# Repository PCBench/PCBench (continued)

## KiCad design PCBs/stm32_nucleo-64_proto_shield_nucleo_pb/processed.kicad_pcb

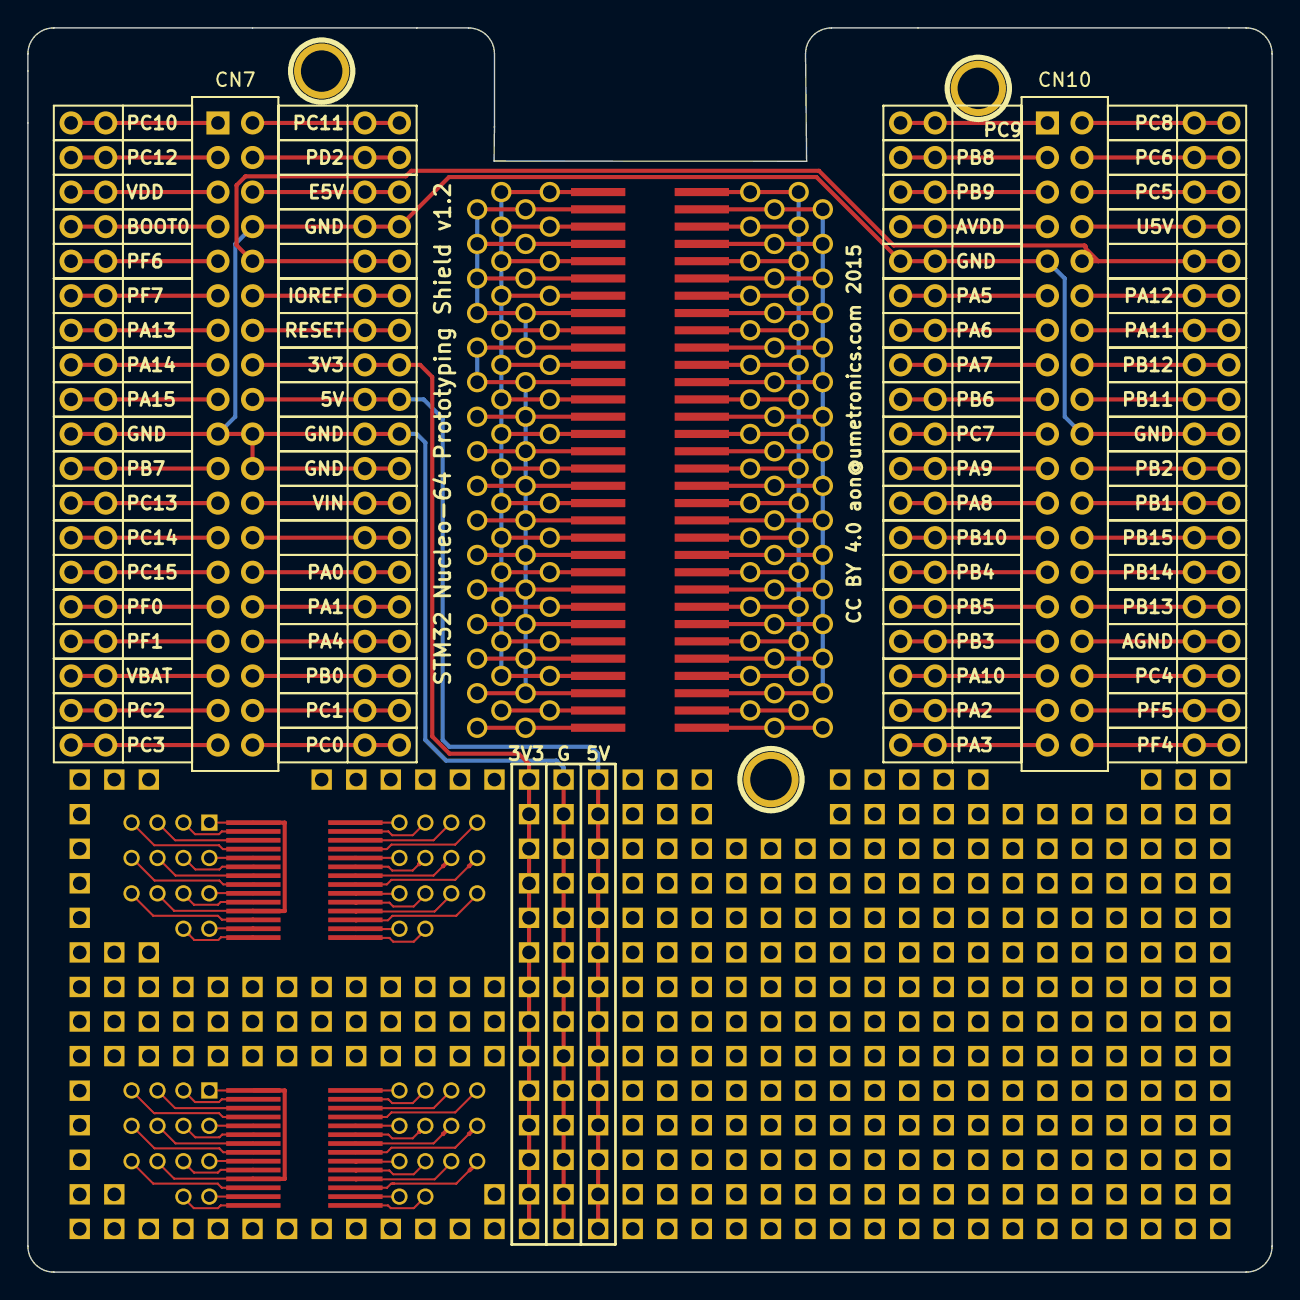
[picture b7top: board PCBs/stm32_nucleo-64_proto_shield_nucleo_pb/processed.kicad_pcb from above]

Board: 2 copper layers, 91.4 x 91.4 mm, 273 parts (0 on the bottom side), 132 nets.

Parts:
1PIN, 1PIN_2, 1PIN_3: P***; 1pin
CN7, CN10: 2X19_HEADER; PIN_ARRAY_19X2
P1, P2, P3, P4, P5, P6, P7, P8, P9, P10, P11, P12, P13, P14, P15, P16, P17, P18, P19, P20, P21, P22, P23, P24, P25, P26, P27, P28, P29, P30, P31, P32, P33, P34, P35, P36, P37, P38, P39, P40, P41, P42, P43, P44, P45, P46, P47, P48, P49, P50, P51, P52, P53, P54, P55, P56, P57, P58, P59, P60, P61, P62, P63, P64, P65, P66, P67, P68, P69, P70, P71, P72, P73, P74, P75, P76: CONN_2
P77, P77_2, P77_3, P77_4, P77_5, P77_6, P77_7, P77_8, P77_9, P77_10, P77_11, P77_12, P77_13, P77_14, P77_15, P77_16: SOIC_AREA
PROTO_1PIN, PROTO_1PIN_2, PROTO_1PIN_3, PROTO_1PIN_4, PROTO_1PIN_5, PROTO_1PIN_6, PROTO_1PIN_7, PROTO_1PIN_8, PROTO_1PIN_9, PROTO_1PIN_10, PROTO_1PIN_11, PROTO_1PIN_12, PROTO_1PIN_13, PROTO_1PIN_14, PROTO_1PIN_15, PROTO_1PIN_16, PROTO_1PIN_17, PROTO_1PIN_18, PROTO_1PIN_19, PROTO_1PIN_20, PROTO_1PIN_21, PROTO_1PIN_22, PROTO_1PIN_23, PROTO_1PIN_24, PROTO_1PIN_25, PROTO_1PIN_26, PROTO_1PIN_27, PROTO_1PIN_28, PROTO_1PIN_29, PROTO_1PIN_30, PROTO_1PIN_31, PROTO_1PIN_32, PROTO_1PIN_33, PROTO_1PIN_34, PROTO_1PIN_35, PROTO_1PIN_36, PROTO_1PIN_37, PROTO_1PIN_38, PROTO_1PIN_39, PROTO_1PIN_40, PROTO_1PIN_41, PROTO_1PIN_42, PROTO_1PIN_43, PROTO_1PIN_44, PROTO_1PIN_45, PROTO_1PIN_46, PROTO_1PIN_47, PROTO_1PIN_48, PROTO_1PIN_49, PROTO_1PIN_50, PROTO_1PIN_51, PROTO_1PIN_52, PROTO_1PIN_53, PROTO_1PIN_54, PROTO_1PIN_55, PROTO_1PIN_56, PROTO_1PIN_57, PROTO_1PIN_58, PROTO_1PIN_59, PROTO_1PIN_60, PROTO_1PIN_61, PROTO_1PIN_62, PROTO_1PIN_63, PROTO_1PIN_64, PROTO_1PIN_65, PROTO_1PIN_66, PROTO_1PIN_67, PROTO_1PIN_68, PROTO_1PIN_69, PROTO_1PIN_70, PROTO_1PIN_71, PROTO_1PIN_72, PROTO_1PIN_73, PROTO_1PIN_74, PROTO_1PIN_75, PROTO_1PIN_76, PROTO_1PIN_77, PROTO_1PIN_78, PROTO_1PIN_79, PROTO_1PIN_80, PROTO_1PIN_81, PROTO_1PIN_82, PROTO_1PIN_83, PROTO_1PIN_84, PROTO_1PIN_85, PROTO_1PIN_86, PROTO_1PIN_87, PROTO_1PIN_88, PROTO_1PIN_89, PROTO_1PIN_90, PROTO_1PIN_91, PROTO_1PIN_92, PROTO_1PIN_93, PROTO_1PIN_94, PROTO_1PIN_95, PROTO_1PIN_96, PROTO_1PIN_97, PROTO_1PIN_98, PROTO_1PIN_99, PROTO_1PIN_100, PROTO_1PIN_101, PROTO_1PIN_102, PROTO_1PIN_103, PROTO_1PIN_104, PROTO_1PIN_105, PROTO_1PIN_106, PROTO_1PIN_107, PROTO_1PIN_108, PROTO_1PIN_109, PROTO_1PIN_110, PROTO_1PIN_111, PROTO_1PIN_112, PROTO_1PIN_113, PROTO_1PIN_114, PROTO_1PIN_115, PROTO_1PIN_116, PROTO_1PIN_117, PROTO_1PIN_118, PROTO_1PIN_119, PROTO_1PIN_120, PROTO_1PIN_121, PROTO_1PIN_122, PROTO_1PIN_123, PROTO_1PIN_124, PROTO_1PIN_125, PROTO_1PIN_126, PROTO_1PIN_127, PROTO_1PIN_128, PROTO_1PIN_129, PROTO_1PIN_130, PROTO_1PIN_131, PROTO_1PIN_132, PROTO_1PIN_133, PROTO_1PIN_134, PROTO_1PIN_135, PROTO_1PIN_136, PROTO_1PIN_137, PROTO_1PIN_138, PROTO_1PIN_139, PROTO_1PIN_140, PROTO_1PIN_141, PROTO_1PIN_142, PROTO_1PIN_143, PROTO_1PIN_144, PROTO_1PIN_145, PROTO_1PIN_146, PROTO_1PIN_147, PROTO_1PIN_148, PROTO_1PIN_149, PROTO_1PIN_150, PROTO_1PIN_151: VAL**; PROTO_1PIN
PROTO_AREA: VAL**; PROTO_AREA
PROTO_AREA_2, PROTO_AREA_3, PROTO_AREA_4, PROTO_AREA_5, PROTO_AREA_6, PROTO_AREA_7, PROTO_AREA_8, PROTO_AREA_9, PROTO_AREA_10, PROTO_AREA_11, PROTO_AREA_12, PROTO_AREA_13, PROTO_AREA_14, PROTO_AREA_15, PROTO_AREA_16, PROTO_AREA_17, PROTO_AREA_18, PROTO_AREA_19, PROTO_AREA_20, PROTO_AREA_21, PROTO_AREA_22, PROTO_AREA_23: VAL**; PROTO_AREA
U1, U1_2: TSSOP28_BREAKOUT

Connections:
/3V3: CN7.16, P27.1, P27.2, PROTO_1PIN_65.10, PROTO_1PIN_75.10, PROTO_1PIN_76.10, PROTO_1PIN_77.10, PROTO_1PIN_78.10, PROTO_1PIN_79.10, PROTO_1PIN_84.10, PROTO_1PIN_88.10, PROTO_1PIN_89.10, PROTO_1PIN_90.10, PROTO_1PIN_91.10, PROTO_AREA_8.3, PROTO_AREA_8.4, PROTO_AREA_8.5
/5V: CN7.18, P28.1, P28.2, PROTO_1PIN_25.10, PROTO_1PIN_63.10, PROTO_AREA_20.1, PROTO_AREA_20.7, PROTO_AREA_20.8, PROTO_AREA_21.2, PROTO_AREA_21.6, PROTO_AREA_21.9, PROTO_AREA_22.2, PROTO_AREA_22.6, PROTO_AREA_22.9, PROTO_AREA_23.1, PROTO_AREA_23.7, PROTO_AREA_23.8
/AGND: CN10.32, P73.1, P73.2
/AVDD: CN10.7, P42.1, P42.2
/BOOT0: CN7.7, P4.1, P4.2
/E5V: CN7.6, P22.1, P22.2
/GND: CN7.8, CN7.19, CN7.20, CN7.22, CN10.9, CN10.20, P10.1, P10.2, P23.1, P23.2, P29.1, P29.2, P30.1, P30.2, P43.1, P43.2, P67.1, P67.2, PROTO_1PIN_64.10, PROTO_1PIN_80.10, PROTO_1PIN_81.10, PROTO_1PIN_82.10, PROTO_1PIN_83.10, PROTO_1PIN_85.10, PROTO_1PIN_86.10, PROTO_1PIN_87.10, PROTO_AREA_21.1, PROTO_AREA_21.7, PROTO_AREA_21.8, PROTO_AREA_22.1, PROTO_AREA_22.7, PROTO_AREA_22.8
/IOREF: CN7.12, P25.1, P25.2
/NC10: CN7.10, CN10.10, P24.1, P24.2, P62.1, P62.2
/NC26: CN7.26, P32.1, P32.2
/PA0: CN7.28, P33.1, P33.2
/PA1: CN7.30, P34.1, P34.2
/PA2: CN10.35, P56.1, P56.2
/PA3: CN10.37, P57.1, P57.2
/PA4: CN7.32, P35.1, P35.2
/PA5: CN10.11, P44.1, P44.2
/PA6: CN10.13, P45.1, P45.2
/PA7: CN10.15, P46.1, P46.2
/PA8: CN10.23, P50.1, P50.2
/PA9: CN10.21, P49.1, P49.2
/PA10: CN10.33, P55.1, P55.2
/PA11: CN10.14, P64.1, P64.2
/PA12: CN10.12, P63.1, P63.2
/PA13: CN7.13, P7.1, P7.2
/PA14: CN7.15, P8.1, P8.2
/PA15: CN7.17, P9.1, P9.2
/PB0: CN7.34, P36.1, P36.2
/PB1: CN10.24, P69.1, P69.2
/PB2: CN10.22, P68.1, P68.2
/PB3: CN10.31, P54.1, P54.2
/PB4: CN10.27, P52.1, P52.2
/PB5: CN10.29, P53.1, P53.2
/PB6: CN10.17, P47.1, P47.2
/PB7: CN7.21, P11.1, P11.2
/PB8: CN10.3, P40.1, P40.2
/PB9: CN10.5, P41.1, P41.2
/PB10: CN10.25, P51.1, P51.2
/PB11: CN10.18, P66.1, P66.2
/PB12: CN10.16, P65.1, P65.2
/PB13: CN10.30, P72.1, P72.2
/PB14: CN10.28, P71.1, P71.2
/PB15: CN10.26, P70.1, P70.2
/PC0: CN7.38, P38.1, P38.2
/PC1: CN7.36, P37.1, P37.2
/PC2: CN7.35, P18.1, P18.2
/PC3: CN7.37, P19.1, P19.2
/PC4: CN10.34, P74.1, P74.2
/PC5: CN10.6, P60.1, P60.2
/PC6: CN10.4, P59.1, P59.2
/PC7: CN10.19, P48.1, P48.2
/PC8: CN10.2, P58.1, P58.2
/PC9: CN10.1, P39.1, P39.2
/PC10: CN7.1, P1.1, P1.2
/PC11: CN7.2, P20.1, P20.2
/PC12: CN7.3, P2.1, P2.2
/PC13: CN7.23, P12.1, P12.2
/PC14: CN7.25, P13.1, P13.2
/PC15: CN7.27, P14.1, P14.2
/PD2: CN7.4, P21.1, P21.2
/PF0: CN7.29, P15.1, P15.2
/PF1: CN7.31, P16.1, P16.2
/PF4: CN10.38, P76.1, P76.2
/PF5: CN10.36, P75.1, P75.2
/PF6: CN7.9, P5.1, P5.2
/PF7: CN7.11, P6.1, P6.2
/RESET: CN7.14, P26.1, P26.2
/U5V: CN10.8, P61.1, P61.2
/VBAT: CN7.33, P17.1, P17.2
/VDD: CN7.5, P3.1, P3.2
/VIN: CN7.24, P31.1, P31.2
unnamed: P77.10, P77.11, P77.12, P77_2.10, P77_2.11, P77_2.12, P77_3.10, P77_3.11, P77_3.12, P77_4.10, P77_4.11, P77_4.12, P77_5.10, P77_5.11, P77_5.12, P77_6.10, P77_6.11, P77_6.12, P77_7.10, P77_7.11, P77_7.12, P77_8.10, P77_8.11, P77_8.12, P77_9.10, P77_9.11, P77_9.12, P77_10.10, P77_10.11, P77_10.12, P77_11.10, P77_11.11, P77_11.12, P77_12.10, P77_12.11, P77_12.12, P77_13.10, P77_13.11, P77_13.12, P77_14.10, P77_14.11, P77_14.12, P77_15.10, P77_15.11, P77_15.12
unnamed: P77.7, P77.8, P77.9, P77_2.7, P77_2.8, P77_2.9, P77_3.7, P77_3.8, P77_3.9, P77_4.7, P77_4.8, P77_4.9, P77_5.7, P77_5.8, P77_5.9, P77_6.7, P77_6.8, P77_6.9, P77_7.7, P77_7.8, P77_7.9, P77_8.7, P77_8.8, P77_8.9, P77_9.7, P77_9.8, P77_9.9, P77_10.7, P77_10.8, P77_10.9, P77_11.7, P77_11.8, P77_11.9, P77_12.7, P77_12.8, P77_12.9, P77_13.7, P77_13.8, P77_13.9, P77_14.7, P77_14.8, P77_14.9, P77_15.7, P77_15.8, P77_15.9
unnamed: P77.4, P77.5, P77.6, P77_2.4, P77_2.5, P77_2.6, P77_3.4, P77_3.5, P77_3.6, P77_4.4, P77_4.5, P77_4.6, P77_5.4, P77_5.5, P77_5.6, P77_6.4, P77_6.5, P77_6.6, P77_7.4, P77_7.5, P77_7.6, P77_8.4, P77_8.5, P77_8.6, P77_9.4, P77_9.5, P77_9.6, P77_10.4, P77_10.5, P77_10.6, P77_11.4, P77_11.5, P77_11.6, P77_12.4, P77_12.5, P77_12.6, P77_13.4, P77_13.5, P77_13.6, P77_14.4, P77_14.5, P77_14.6, P77_15.4, P77_15.5, P77_15.6
unnamed: P77.1, P77.2, P77.3, P77_2.1, P77_2.2, P77_2.3, P77_3.1, P77_3.2, P77_3.3, P77_4.1, P77_4.2, P77_4.3, P77_5.1, P77_5.2, P77_5.3, P77_6.1, P77_6.2, P77_6.3, P77_7.1, P77_7.2, P77_7.3, P77_8.1, P77_8.2, P77_8.3, P77_9.1, P77_9.2, P77_9.3, P77_10.1, P77_10.2, P77_10.3, P77_11.1, P77_11.2, P77_11.3, P77_12.1, P77_12.2, P77_12.3, P77_13.1, P77_13.2, P77_13.3, P77_14.1, P77_14.2, P77_14.3, P77_15.1, P77_15.2, P77_15.3
unnamed: U1.19, U1.191
unnamed: U1.10, U1.101
unnamed: U1.20, U1.201
unnamed: U1.21, U1.211
unnamed: U1.18, U1.181
unnamed: U1.14, U1.141
unnamed: U1.6, U1.61
unnamed: U1.7, U1.71
unnamed: U1.8, U1.81
unnamed: U1.9, U1.91
unnamed: U1.12, U1.121
unnamed: U1.22, U1.221
unnamed: U1.13, U1.131
unnamed: U1.23, U1.231
unnamed: U1.24, U1.241
unnamed: U1.15, U1.151
unnamed: U1.25, U1.251
unnamed: U1.16, U1.161
unnamed: U1.26, U1.261
unnamed: U1.17, U1.171
unnamed: U1.27, U1.271
unnamed: U1.5, U1.51
unnamed: U1.28, U1.281
unnamed: U1.1, U1.11
unnamed: U1.2, U1.21
unnamed: U1.3, U1.31
unnamed: U1.4, U1.41
unnamed: P77_16.1, P77_16.2, P77_16.3
unnamed: P77_16.4, P77_16.5, P77_16.6
unnamed: P77_16.7, P77_16.8, P77_16.9
unnamed: P77_16.10, P77_16.11, P77_16.12
unnamed: U1_2.1, U1_2.11
unnamed: U1_2.2, U1_2.21
unnamed: U1_2.3, U1_2.31
unnamed: U1_2.4, U1_2.41
unnamed: U1_2.5, U1_2.51
unnamed: U1_2.6, U1_2.61
unnamed: U1_2.7, U1_2.71
unnamed: U1_2.8, U1_2.81
unnamed: U1_2.9, U1_2.91
unnamed: U1_2.10, U1_2.101
unnamed: U1_2.12, U1_2.121
unnamed: U1_2.13, U1_2.131
unnamed: U1_2.14, U1_2.141
unnamed: U1_2.15, U1_2.151
unnamed: U1_2.16, U1_2.161
unnamed: U1_2.17, U1_2.171
unnamed: U1_2.18, U1_2.181
unnamed: U1_2.19, U1_2.191
unnamed: U1_2.20, U1_2.201
unnamed: U1_2.21, U1_2.211
unnamed: U1_2.22, U1_2.221
unnamed: U1_2.23, U1_2.231
unnamed: U1_2.24, U1_2.241
unnamed: U1_2.25, U1_2.251
unnamed: U1_2.26, U1_2.261
unnamed: U1_2.27, U1_2.271
unnamed: U1_2.28, U1_2.281
